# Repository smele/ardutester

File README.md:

# ardutester

#Work in progress...

An ATmega328 µC Component Tester based on work of ArduTester ver. 0.7f 

 Original Source from:        http://www.mikrocontroller.net/articles/AVR-Transistortester
 Original Software:           by Karl-Heinz Kuebbeler (kh_kuebbeler@web.de)
                              The Ardutester software is based on porting by Markus Reschke (madires@theca-tabellaria.de) 
 
 Schematic & Home Page:       
 
 Arduino version:             PighiXXX
                              PaoloP 
 
 - ONLY TTL COMPONENTS!

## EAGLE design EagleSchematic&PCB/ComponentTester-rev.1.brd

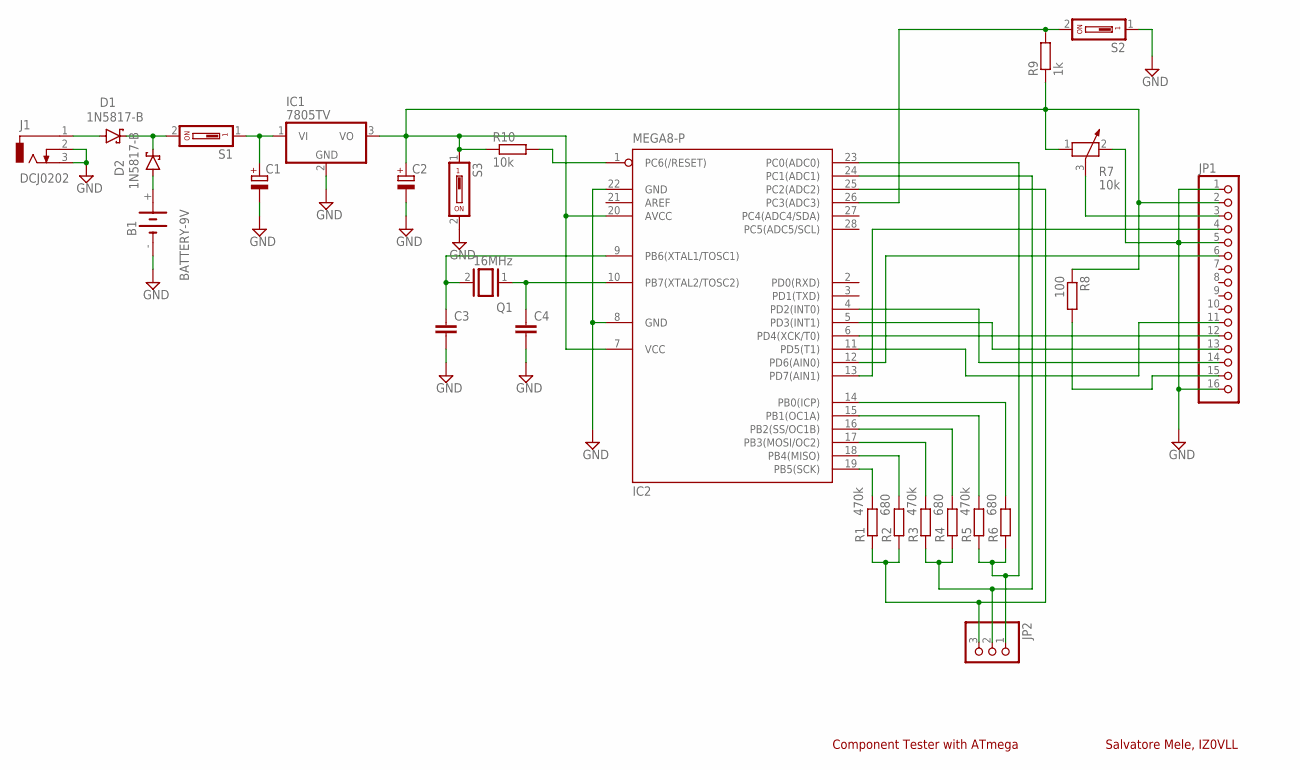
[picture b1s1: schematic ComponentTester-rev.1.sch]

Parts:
B1: BATTERY-9V; 9V-BATTERY-SNAP
C1, C2: CPOL-EUE2.5-6; E2,5-6
C3, C4: C-EU025-024X044; C025-024X044
D1, D2: 1N5817-B; DO41-7.6
IC1: 7805TV; TO220V
IC2: MEGA8-P; DIL28-3
J1: DCJ0202
JP1: PINHD-1X16; 1X16
JP2: PINHD-1X3; 1X03
Q1: 16MHz; QS
R1, R3, R5: 470k; 0207/10
R2, R4, R6: 680; 0207/10
R7: 10k; PT-10S
R8: 100; 0207/10
R9: 1k; 0207/10
R10: 10k; 0207/10
S1, S2, S3: SD4-01

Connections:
GND: B1.-, C1.-, C2.-, C3.2, C4.2, IC1.2 (GND), IC2.8 (GND), IC2.22 (GND), J1.2, J1.3, JP1.1, JP1.5, JP1.16, R7.2, S2.1, S3.2
unnamed: C1.+, IC1.1 (VI), S1.1
unnamed: C2.+, IC1.3 (VO), IC2.7 (VCC), IC2.20 (AVCC), JP1.2, R7.1, R8.1, R9.1, R10.1, S3.1
unnamed: IC2.14 (PB0(ICP)), R6.2
unnamed: IC2.15 (PB1(OC1A)), R5.2
unnamed: IC2.16 (PB2(SS/OC1B)), R4.2
unnamed: IC2.17 (PB3(MOSI/OC2)), R3.2
unnamed: IC2.18 (PB4(MISO)), R2.2
unnamed: IC2.19 (PB5(SCK)), R1.2
unnamed: IC2.25 (PC2(ADC2)), JP2.3, R1.1, R2.1
unnamed: IC2.24 (PC1(ADC1)), JP2.2, R3.1, R4.1
unnamed: IC2.23 (PC0(ADC0)), JP2.1, R5.1, R6.1
unnamed: JP1.3, R7.3
unnamed: IC2.26 (PC3(ADC3)), R9.2, S2.2
unnamed: IC2.13 (PD7(AIN1)), JP1.4
unnamed: IC2.12 (PD6(AIN0)), JP1.6
unnamed: IC2.4 (PD2(INT0)), JP1.14
unnamed: IC2.5 (PD3(INT1)), JP1.13
unnamed: IC2.6 (PD4(XCK/T0)), JP1.12
unnamed: IC2.11 (PD5(T1)), JP1.11
unnamed: JP1.15, R8.2
unnamed: C4.1, IC2.10 (PB7(XTAL2/TOSC2)), Q1.1
unnamed: C3.1, IC2.9 (PB6(XTAL1/TOSC1)), Q1.2
unnamed: IC2.1 (PC6(/RESET)), R10.2
unnamed: D1.A, J1.1
unnamed: B1.+, D2.A
unnamed: D1.C, D2.C, S1.2

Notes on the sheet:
Component Tester with ATmega
Salvatore Mele, IZ0VLL

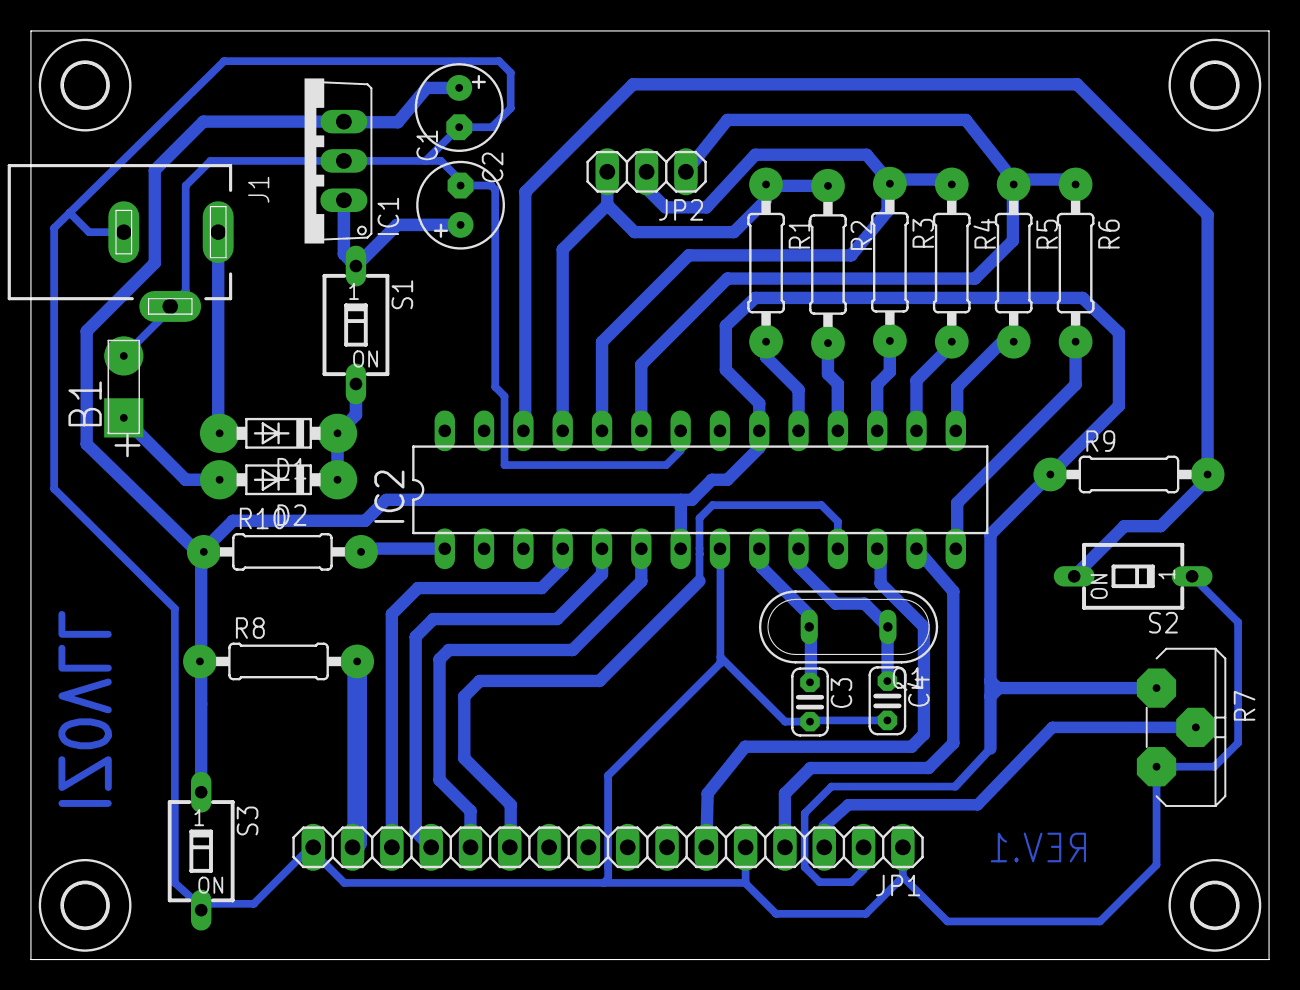
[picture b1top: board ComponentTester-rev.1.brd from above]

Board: 2 copper layers, 80.0 x 60.0 mm, 30 parts (0 on the bottom side), 27 nets.

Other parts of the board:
U$1, U$2, U$3, U$4: 2,8

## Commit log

2019-09-28 Schema and PCB.
